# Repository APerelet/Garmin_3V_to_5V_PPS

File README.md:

# Garmin_3V_to_5V_PPS
Avoid buying the A300 from Campbell Scientific for >100$. This cheap to print board provides the same functionality in a smaller and cheaper package.

Parts required listed below. Any Part of similar spec should work, but Digikey part numbers are provided for the components originally used. Strongly recomended to coat board with a conformal coating to prevent accidental shorting if used without a back covering.

*.zip file contains gerber files

*.brd is Autodesk Eagle board file

*.sch is Autodesk Eagle schematic file

# Circuit Schematic

### BOM (Digikey part numbers)
- Terminal block: 4 position, 2.54mm pin spacing (ED10563-ND)
- Op-Amp: single circuit, 8-DIP (296-34453-5-ND) 
- Resistor: 1 KOhm, 1%, 1/4 W (S1KCACT-ND)
- Resistor: 1.5 KOhm, 1%, 1/4 W (S1.5KCACT-ND)

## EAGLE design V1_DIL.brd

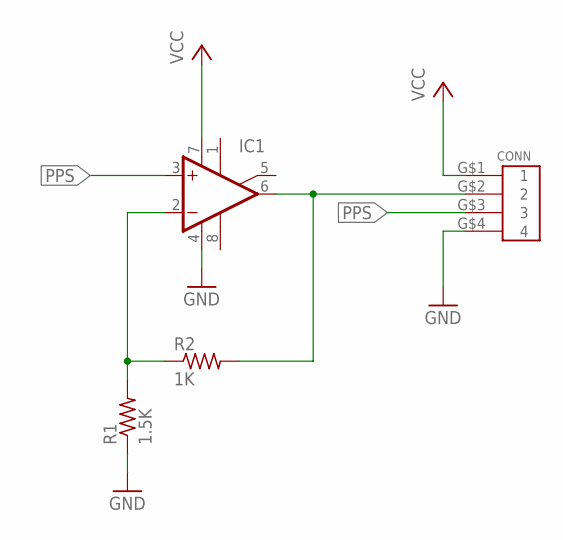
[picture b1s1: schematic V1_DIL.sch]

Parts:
CONN: OSTVN04A150
IC1: LM741P; DIL08
R1: 1.5K; 0204/7
R2: 1K; 0204/7

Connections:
GND: CONN.G$4 (4), IC1.4 (V-), R1.1
IN-: IC1.2 (-IN), R1.2, R2.1
OUT: CONN.G$2 (2), IC1.6 (OUT), R2.2
PPS: CONN.G$3 (3), IC1.3 (+IN)
VCC: CONN.G$1 (1), IC1.7 (V+)

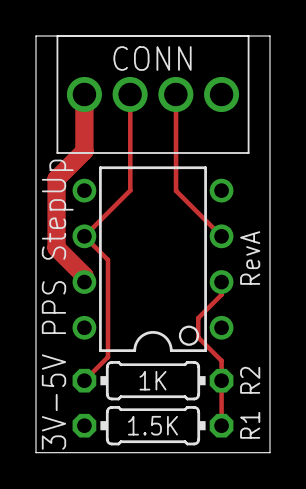
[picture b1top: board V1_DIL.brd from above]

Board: 2 copper layers, 13.0 x 23.1 mm, 4 parts (0 on the bottom side), 5 nets.

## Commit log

2019-05-20 initial

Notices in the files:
parts and their libraries:
SparkFun-Connectors: Licensing: Creative Commons ShareAlike 4.0 International - https://creativecommons.org/licenses/by-sa/4.0
